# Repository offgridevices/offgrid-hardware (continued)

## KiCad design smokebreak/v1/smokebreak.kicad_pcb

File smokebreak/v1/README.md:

# SmokeBreak v1

**A smoke stopper you hold in one hand.** The battery plugs into one end and
the drone's lead into the other. Before the drone gets full battery power,
SmokeBreak checks it with a gentle 3 V probe. A short, a half-short or a
reversed lead is caught there, and nothing burns. The drone's capacitors are
then charged slowly through resistors. Only after that does the main switch
close, behind a guarded flip-up toggle.

Plug a pack's balance lead into its socket and SmokeBreak also reads every
cell (2S–6S), the pack's balance and its internal resistance. It remembers
each pack by number.

> **Status: design complete, not yet built.**
> - The board is fully routed: KiCad 10 DRC 0 errors, 0 warnings, 0 unconnected.
> - Its nets match the circuit pad for pad.
> - The power-path simulations pass (21 of 21), and so do the firmware model's 328 tests.
> - The printed case passes its fit check against the board.
>
> Nothing has been measured on hardware yet: build a few and go through
> *Bring-up* before a larger order.

## This revision

| | |
|---|---|
| Revision | **v1** (product: [`../README.md`](../README.md)) |
| Status | designed, not yet built |
| Tests and simulations | [`TESTS.md`](TESTS.md): every one with its v1 result |
| Trade-offs | [`docs/decisions.md`](docs/decisions.md) |
| Parts availability | [`docs/parts-check-2026-10-18.md`](docs/parts-check-2026-10-18.md) (check again before ordering) |
| How the circuit works | [`docs/architecture.md`](docs/architecture.md) |
| Spec, concepts, design studies | [`../design/`](../design/) (shared by every revision) |
| Toolchain | KiCad 10.0.7 (pinned image, `tools/Dockerfile`), Freerouting 2.5.0, ngspice 47, CadQuery 2.8 |
| Brand | OffGrid v3.2.2 ([`docs/brand.md`](../../docs/brand.md)); checked by `tools/verify_brand.py` |

| | |
|---|---|
| Case | 97 × 56 × 15 mm, G2 (curvature-continuous) corners, printed in three colours; the switch guard stands 17.9 mm above the face |
| Batteries | 2S–14S LiPo, LiHV, Li-ion (6–60.9 V); a 1S pack works when USB powers the box. XT60 and XT30 male |
| Drone | XT60 (12 AWG) and XT30 (16 AWG) female leads; 15 A continuous, 25 A for 60 s |
| Balance lead | five JST-XH sockets, 2S to 6S, in a well in the face |
| Screen | 2.25" 76 × 284 colour bar (EastRising ER-TFT2.25-1) |
| Controls | guarded flip-up toggle (up = on) inside a 12-LED status ring; one Limit rocker (− / +); beeper |
| Protection | 4 µs short-circuit cut-off, current limit, reversed-battery blocking on both sides, a 40 A fire fuse, refuses packs above 62.5 V |
| PCB | 91.6 × 50.6 mm, 6 layers, 1.6 mm, 1 oz copper on every layer, black mask, white silk, ENIG |

## Requirements

What the owner set, and where v1 stands.

| Requirement | v1 |
|---|---|
| Stops a short before it smokes | ✅ 3 V probe first; 4 µs cut-off when on (simulation case 3) |
| Survives wrong connections: reversed pack, pack on the drone side, both sides | ✅ simulations cases 2, 4, 5, 6 |
| Per-cell battery check, 2S–6S | ✅ divider network on 0.1 % resistors; firmware model tests |
| Fire safety if a part inside fails | ✅ soldered 40 A / 80 V fuse (`docs/decisions.md`) |
| Survives a pack bigger than 14S by mistake | ✅ 100 V supply chip; the screen says "too high" and it will not arm |
| Thin, small, one-hand use, does not rock when armed | ✅ 15 mm case, rubber feet, finger lip under the back edge |
| Perfectionist face: one 6 mm margin everywhere, G2 corners, screen corners matched in the UI | ✅ `src/geometry.py`, read by the board and the case |
| One rocker; text only "2S…6S" and "LIMIT" | ✅ multi-colour inlays, 2.5 mm caps, strokes ≥ 0.44 mm |
| Orderable from PCBWay, SMD parts assembled on one side | ✅ `production/` |
| Case printable on a multi-material printer | ✅ `enclosure/print/`: watertight STLs, fit check passes |
| Landed cost $20–22 (owner, 11 Oct 2026) | ❌ about **$55.60** at 100 units (`tools/cost.py`, display included): the two flat pre-charge resistors (≈ $14.70) and the toggle (≈ $10.20) are most of the gap. Accepted for v1 (owner, 1 Nov 2026); to bring down later (*Next steps*) |
| 15 A continuous in the closed case | ⏳ not yet checked for heat (*Limits*) |

## Next steps

1. **Bring the cost down (later).** v1 is accepted at about $55.60 (owner,
   1 Nov 2026). The places to look: same-footprint pre-charge resistors,
   and a short-lever toggle (which would also make the guard lower). Either
   part change re-runs the routing and every check, so it goes into `v2/`.
2. **Confirm the display's controller with EastRising.** The firmware
   model and the screens assume an ST7789P3. BuyDisplay's own page lists an
   **NV3023B** for the bare ER-TFT2.25-1, and the ST7789P3 for the
   ER-TFTM2.25-1 (the same panel on a breakout board). Ask which controller
   the bare module ships with. If it is the NV3023B, the firmware needs its
   driver (same pins, different init). Check the FPC's contact side against
   J7 too.
3. **Order 5 prototypes** (*Ordering*) and print one case (*Printing*).
4. **Bring them up** (*Bring-up*). Then measure what the simulations
   predict: pre-charge time and resistor heat, short cut-off time, and the
   temperature of the FETs at 15 A in the closed case. Record the results
   in `TESTS.md`.
5. **Write the real firmware** from the model in `firmware/` (every
   decision there is specified and tested).
6. Changes that need new copper go into `v2/`.

## Ordering the board (PCBWay)

1. **PCB:** upload `production/smokebreak-gerbers.zip`.
   - 6 layers, 91.6 × 50.6 mm, FR-4 TG150, 1.6 mm.
   - **1 oz copper on the outer and the inner layers** (the battery current runs on the inner planes).
   - Min track/space 4/4 mil, min hole 0.2 mm.
   - **Black** mask, **white** silkscreen, **ENIG**, vias tented.
2. **Assembly:** turnkey, top side only. Upload
   `production/smokebreak-bom-pcbway.csv` and `production/smokebreak-cpl.csv`.
   - LCSC has no stock of the fuse (**2822HC40-RTR**) or the pre-charge
     resistors (**D2TO020C3R900FRE3**), and only 3 of the TVS diode
     (**SMBJ64CA**) on 18 Oct 2026. Their BOM lines ask PCBWay to source the
     first two by part number from Digi-Key or Mouser. The TVS is a standard
     part that several makers produce. Details:
     [`docs/parts-check-2026-10-18.md`](docs/parts-check-2026-10-18.md).
   - The THT lines are not fitted; they ship loose: XT60PW-M, XT30PW-M,
     JST B3B/B4B/B5B/B6B/B7B-XH-A (one each), the C&K 7107 toggle, and the
     two drone leads (XT60H female on 12 AWG, XT30U female on 16 AWG, 50–75 mm).
3. **Display:** EastRising ER-TFT2.25-1 (76 × 284, 8-pin 0.5 mm FPC),
   bought separately. Ask for the IPS version.

## Printing the case

The files are in `enclosure/print/`. Use a 0.4 mm nozzle, 0.2 mm layers,
and PETG or ASA (PLA softens in a hot car).

| Part | Colour | Orientation | Notes |
|---|---|---|---|
| `top.stl` | main | face down | supports only inside the balance well (its floor plate is a bridge 2.7 mm up) |
| `text_inlay.stl` | white | with the top | same print job, second filament |
| `ring_inlay.stl` | translucent | with the top | same print job, third filament |
| `bottom.stl` | main | inside up | flat |
| `guard.stl` | accent | on its side | |
| `rocker.stl` | main | cap down | |

Hardware:
- 3 × M3 heat-set inserts (M3 × 5.7)
- 3 × M3 × 8 button-head screws
- 4 × Ø10 mm rubber feet (Bumpon)
- a Ø2 × 20 mm steel dowel (guard hinge)
- a Ø2 × 12 mm steel dowel (rocker pivot)
- a Ø6 × 3 mm N52 disc magnet (glued into the guard's tip)

The STEP models of every part, and the assembly, are in
`mechanical/smokebreak-enclosure-step.zip`. The fit check's full report is
`enclosure/print/fit_check.txt`.

## Assembly

1. **Balance sockets:** J12 (2S), J11 (3S), J10 (4S), J9 (5S) and J5 (6S),
   mouths up. Pin 1 (the square pad) goes at the front. The bottom silkscreen
   names each socket and points an arrow at pin 1 (the black wire).
2. **Battery plugs:** XT60 (J1) and XT30 (J2) male at the battery end. Seat
   them fully and use a big iron (the pads sit on power planes).
3. **Drone leads:** strip 5 mm and tin. The XT60 lead goes to J3 and the
   XT30 lead to J4, red to + (marked on both sides of the board).
4. **Toggle SW1 last,** lever upright.
5. **Trim every lead to 1.0 mm or less** under the board (the floor leaves 1.3 mm).
6. **Case:**
   1. Press the inserts into the top shell.
   2. Slide the guard's pin along its groove, then fit the guard.
   3. Fit the rocker and its pin.
   4. Tape the display into its pocket, with the FPC folded under to J7.
   5. Drop the board in.
   6. Hook the floor's tongue into the battery-end groove and close the
      floor. Its end tab clamps the drone leads.
   7. Fit the three screws.

## Bring-up

1. **Bare board:** check there are no shorts VIN–GND, VOUT–DRONE_NEG,
   +5V–GND or +3V3–GND.
2. **USB-C only:** +5V should read about 4.7 V and +3V3 should read 3.3 V.
   Flash over the SWD pads on the underside (J6) or USB DFU.
3. **Bench supply** at 12 V with a 100 mA limit, into the battery XT60,
   guard closed. The screen wakes, and nothing appears on the drone side.
4. **Reverse the bench supply:** nothing happens and nothing gets warm.
5. **Probe tests** with resistors on the drone side: open, 1 kΩ, 18 Ω,
   0.3 Ω. Then a 2200 µF capacitor bank for the pre-charge. Then a real drone.
6. **Measure and set in firmware:** the board's own capacitance on VOUT as
   the probe sees it, the current amplifier's offset, and the cell-divider gains.

## Limits

- **Heat at 15 A is not simulated.** The FETs (Q1, Q2 about 4 mΩ each, Q11
  about 8 mΩ) make about 4 W together at 15 A inside a closed printed case.
  Measure at bring-up before rating the box above short motor tests.
- **The pre-charge resistors' pulse rating** is read off the datasheet
  curve (about 10 J each at 100 ms). The firmware's 12 J abort puts 6 J on
  each. Bench-test repeated attempts and set the cool-down from the
  thermistor.
- **1S packs** need USB power: the 5 V supply starts at 6 V.
- **The guard sensor** reads "open" only once the guard is past about 40°.
  A guard that is only partly lifted counts as closed.
- **Simulation open risks** (models read off datasheet graphs, the short
  cut-off timing, capacitor DC bias) are listed in `sim/SIM.md`.

## Building it again

Everything here is generated by the scripts in `src/`, `enclosure/` and
`sim/`. Run them inside the pinned toolchain (`tools/Dockerfile`; `tools/kd`
runs a command in it).

| What | Command (from `smokebreak/v1`) | Notes |
|---|---|---|
| Silkscreen art on the routed board | `python3 src/artwork.py` | what CI runs |
| Production files, STEP, renders, DRC and net gates | `python3 src/fab.py` | `--no-3d` for the production files and gates only |
| Check the committed files | `python3 tools/check_outputs.py` | after the two above |
| Firmware model tests | `python3 -m pytest -q firmware/tests` | |
| Simulations | `cd sim && python3 run_all.py` | writes `sim/SIM.md` and `sim/plots/` |
| Brand check | `python3 tools/verify_brand.py` | needs Chromium |
| Case | `python3 enclosure/dump_board.py` (KiCad's Python), then `enclosure.py --no-dump` and `check.py` (a Python with CadQuery 2.8 and trimesh), `render.py` (Blender's Python, previews), `package.py` | see `enclosure/README.md` |
| The whole board from the circuit | `bash src/pipeline.sh` | about 3 hours; routing differs run to run, so the committed board stays the design of record |

The routed board (`smokebreak.kicad_pcb`) is the design of record. CI does
not route the board again; it rebuilds the art and every production file from
the routed board, and fails if they differ from what is committed.

## What is where

| Path | What |
|---|---|
| `smokebreak.kicad_pcb` / `.kicad_pro` / `.kicad_dru` | the routed board (KiCad 10) |
| `production/` | Gerber zip, PCBWay BOM, pick-and-place, netlist |
| `mechanical/` | the board in 3D (`smokebreak-step.zip`), the case parts in 3D (`smokebreak-enclosure-step.zip`) |
| `enclosure/` | the case as code (CadQuery), its fit check, and `print/` (the STLs) |
| `images/` | renders of the board and the case |
| `src/` | the board as code: `geometry.py` (every mechanical number), `circuit.py`, `parts.py`, `place.py`, the router steps, `artwork.py`, `fab.py` |
| `lib/` | footprints and 3D models |
| `fonts/` | the brand fonts the silkscreen and case text are drawn in (OFL) |
| `sim/` | power-path simulations and their report |
| `firmware/` | reference model of every firmware decision, with tests |
| `ui/` | the screens, drawn at the panel's real resolution |
| `tools/` | toolchain (Dockerfile), output check, brand check, cost tally, debug plots |
| `docs/` | decisions, architecture, the dated parts check |
| [`../design/`](../design/) | before any revision: the original spec, market research, the 20 concepts and the design studies |

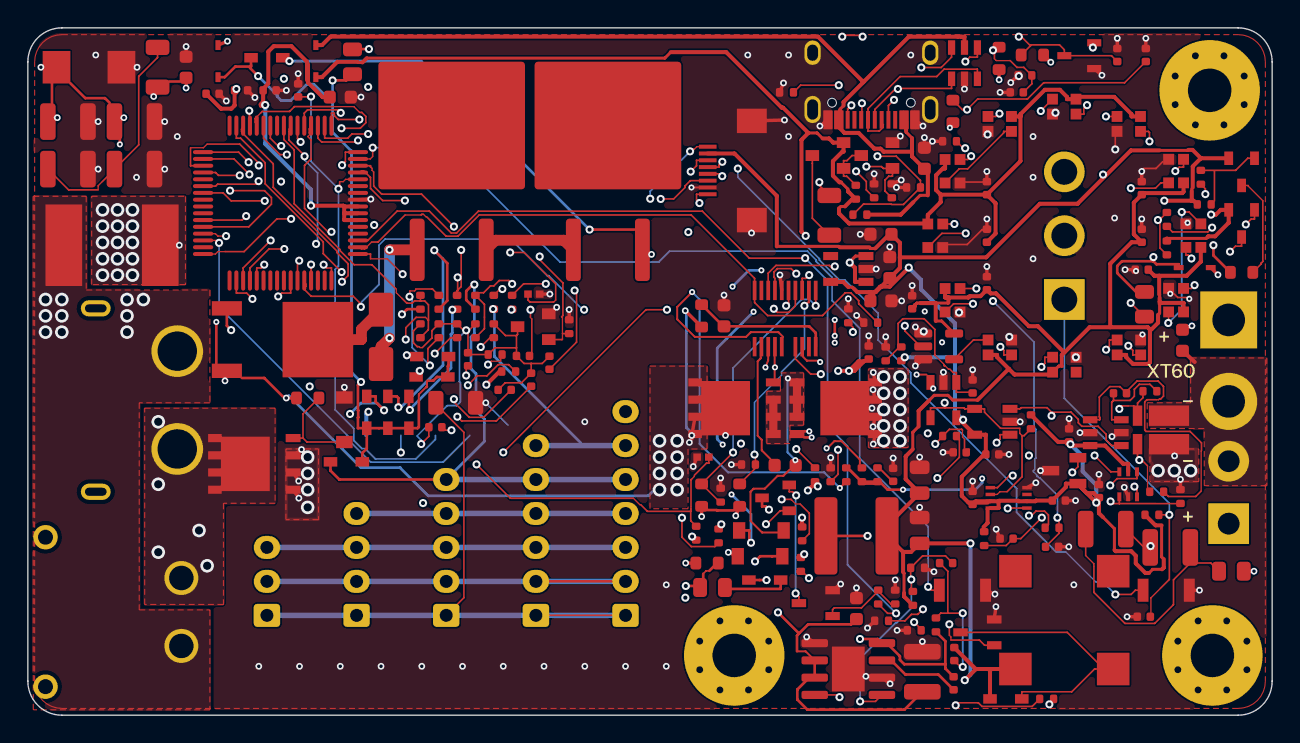
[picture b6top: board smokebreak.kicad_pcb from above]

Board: 6 copper layers, 91.6 x 50.6 mm, 208 parts (1 on the bottom side), 123 nets.

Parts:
BZ1: MLT-8530; BUZ-SMD_4P-L8.5-W8.5-P8.50-BR
C1, C2, C26: 2u2F 100V; C_1210_3225Metric
C3, C4, C14, C27: 100nF 100V; C_0603_1608Metric
C5, C32, C41, C49: 1uF 25V; C_0603_1608Metric
C6, C8, C16: 1nF 50V; C_0402_1005Metric
C7, C10, C11, C12, C13, C15, C17, C18, C19, C20, C21, C22, C23, C34, C35, C36, C38, C42, C43, C44, C45, C46, C47, C48, C55, C56: 100nF 16V; C_0402_1005Metric
C9, C39, C40: 10nF 50V; C_0402_1005Metric
C28: 3n3F 50V; C_0402_1005Metric
C29: 2n2F 50V; C_0402_1005Metric
C30, C31: 10uF 10V; C_0805_2012Metric
C33, C37: 4u7F 10V; C_0603_1608Metric
C50, C51, C52, C53: 4u7F 100V; C_1210_3225Metric
C54: 22nF 50V; C_0402_1005Metric
C57: 56pF 50V; C_0402_1005Metric
D1: SMBJ64CA; SMB_L4.6-W3.6-LS5.3-BI
D2: 10 V; SOD-123_L2.7-W1.6-LS3.7-RD
D3: SS2H10; D_SMA
D4, D14, D16: BAT46WJ; SOD-323F_L2.0-W1.6-LS2.5-RD
D5: BAT54S; SOT-23-3_L3.0-W1.7-P0.95-LS2.9-BR
D6, D7, D8, D9, D10, D11, D15, D17, D19: 1N4148WS; SOD-323_L1.8-W1.3-LS2.5-RD
D18: 15 V; SOD-123_L2.7-W1.6-LS3.7-RD
D20: 12 V; SOD-123_L2.7-W1.6-LS3.7-RD
F1: 40 A 80 V; Fuse_Eaton_2822HC
H1, H2, H3: M3; MountingHole_M3_Washer
J1: XT60 male; CONN-TH_XT60PW-M
J2: XT30 male; CONN-TH_XT30PW-M
J3: XT60 female lead; WirePads_12AWG_NS
J4: XT30 female lead; WirePads_16AWG_NS
J5: JST-XH 6S; JST_XH_B7B-XH-A_1x07_P2.50mm_Vertical_Tight
J6: SWD; SWD_Pads_1x5_P2.54
J7: ER-TFT2.25-1 FPC; Hirose_FH12-8S-0.5SH_1x08-1MP_P0.50mm_Horizontal
J8: USB-C; USB-C_SMD-TYPE-C-31-M-12_1
J9: JST-XH 5S; JST_XH_B6B-XH-A_1x06_P2.50mm_Vertical_Tight
J10: JST-XH 4S; JST_XH_B5B-XH-A_1x05_P2.50mm_Vertical_Tight
J11: JST-XH 3S; JST_XH_B4B-XH-A_1x04_P2.50mm_Vertical_Tight
J12: JST-XH 2S; JST_XH_B3B-XH-A_1x03_P2.50mm_Vertical_Tight
L1: 47 uH; L_Changjiang_FNR6045S
LED1, LED2, LED3, LED4, LED5, LED6, LED7, LED8, LED9, LED10, LED11, LED12: WS2812B-2020; LED-SMD_4P-L2.2-W2.0-P1.00_WS2815C-2020-4P
Q1: input FET; PG-TDSON-8_L5.9-W5.1-P1.27-LS6.1-BL
Q2: output FET; PG-TDSON-8_L5.9-W5.1-P1.27-LS6.1-BL
Q3: SUD50P10-43L; TO-252-3_L6.5-W5.8-P4.58-BR
Q4: MMBTA42; SOT-23-3_L2.9-W1.3-P1.90-LS2.4-BR
Q5, Q10: BC817; SOT-23-3_L2.9-W1.6-P1.90-LS2.8-BR
Q6, Q7: MMBT5401; SOT-23-3_L2.9-W1.3-P1.90-LS2.4-BR
Q8, Q12: 2N7002; SOT-23_L2.9-W1.3-P1.90-LS2.4-BR
Q9: AO3401A; SOT-23_L2.9-W1.3-P1.90-LS2.4-BR
Q11: BSC070N10LS5; PG-TDSON-8_L5.9-W5.1-P1.27-LS6.1-BL
R1: 10 Ohm; R_0603_1608Metric
R2, R4, R30, R33: 1 M; R_0603_1608Metric
R3: 470 k; R_0402_1005Metric
R5: 19.6 k; R_0402_1005Metric
R6, R10, R13, R18, R23, R24, R26, R27, R37, R39, R41, R43, R45, R47, R52, R60, R64, R65, R79, R80: 100 k; R_0402_1005Metric
R7: 1 M; R_0402_1005Metric
R8, R11, R12, R21, R22, R25, R35, R66: 10 k; R_0402_1005Metric
R9: 40.2 k; R_0402_1005Metric
R14, R15: 10 Ohm; R_0402_1005Metric
R16: 100 Ohm; R_0402_1005Metric
R17, R54, R55, R61, R69, R71: 1 k; R_0402_1005Metric
R19, R32: 100 k; R_0603_1608Metric
R20: 47 k; R_0805_2012Metric
R28: 1 k; R_0603_1608Metric
R29: 100 Ohm; R_0805_2012Metric
R31, R34: 52.3 k; R_0402_1005Metric
R36: 47 k; R_0402_1005Metric
R38: 200 k; R_0402_1005Metric
R40: 357 k; R_0402_1005Metric
R42: 499 k; R_0402_1005Metric
R44: 649 k; R_0402_1005Metric
R46: 787 k; R_0402_1005Metric
R53: 10 Ohm; R_0805_2012Metric
R56: 33 Ohm; R_1206_3216Metric
R62, R63: 5.1 k; R_0402_1005Metric
R67: 0.33 Ohm; R_1206_3216Metric
R68: 0.47 Ohm; R_0805_2012Metric
R70: 49.9 k; R_0402_1005Metric
R72: 4.7 k; R_0402_1005Metric
R73: 820 Ohm; R_0402_1005Metric
R74: 4.7 M; R_0603_1608Metric
R75: 10 Ohm; R_1206_3216Metric
R76: 30.9 k; R_0402_1005Metric
R77: 453 k; R_0402_1005Metric
R78: 143 k; R_0402_1005Metric
RS1: 1 mOhm; RES-SMD_4P-L3.8-W3.1
RT1, RT2: 10 k NTC; R0402
R_PRE, R_PRE2: 3.9 Ohm 20 W; TO-263-2
SW1: ON-OFF-(ON); SW_Toggle_SPDT_P4.70mm_THT
SW2: Limit -; KEY-SMD_B3U-1000PM
SW3: Limit +; KEY-SMD_B3U-1000PM
U1: TPS48000; VSSOP-19_L5.1-W3.0-P0.50-LS4.9
U2: INA181A2; SOT-23-6_L2.9-W1.6-P0.95-LS2.8-BL
U3: LM5164DDAR; SOIC-8-1EP_3.9x4.9mm_P1.27mm_EP2.41x3.3mm
U4: TLV75533; SOT-23-5_L3.0-W1.7-P0.95-LS2.8-BR
U5: STM32G0B1RBT6; LQFP-64_L10.0-W10.0-P0.50-LS12.0-BL
U6: DRV5032FA; SOT-23-3_L2.9-W1.3-P0.95-LS2.4-BR
U7: 74LVC1G11; SC-88-6_L2.0-W1.3-P0.65-LS2.1-BL
U8, U12: LMV331; SOT-23-5_L3.0-W1.7-P0.95-LS2.8-BR
U9: SN74LVC1G74; SSOP-8_L2.0-W2.3-P0.50-LS3.1-BR
U10: SN74AHCT1G125; SOT-23-5
U11: USBLC6-2SC6; SOT-23-6_L2.9-W1.6-P0.95-LS2.8-BL

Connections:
+3V3: C7.1, C10.1, C11.1, C12.1, C13.1, C32.1, C33.1, C34.1, C35.1, C36.1, C37.1, C41.1, C56.1, D5.2, J6.1, J7.7, Q6.2, Q7.2, R8.1, R11.2, R12.2, R25.1, R26.2, R27.2, R35.1, R54.2, R55.2, R66.2, R70.1, U2.6, U4.5, U5.6, U5.7, U5.8, U6.1, U7.5, U8.5, U9.2, U9.7, U9.8, U12.5
+5V: BZ1.1, C28.2, C30.1, C31.1, C42.1, C43.1, C44.1, C45.1, C46.1, C47.1, C48.1, D16.1, D17.1, L1.2, LED1.4, LED2.4, LED3.4, LED4.4, LED5.4, LED6.4, LED7.4, LED8.4, LED9.4, LED10.4, LED11.4, LED12.4, Q9.2, R77.1, R80.1, U4.1, U4.3, U10.5
ARM_CLK: U5.60, U9.1
AUX: D6.1, D7.1, D8.1, D9.1, D10.1, D11.1, D14.1, D15.1, R53.1
AUX_F: C26.1, C27.1, R53.2, U3.2, U3.3
BAL1: J5.1, J9.1, J10.1, J11.1, J12.1, R75.1
BAL2: D6.2, J5.2, J9.2, J10.2, J11.2, J12.2, R36.1
BAL2_ADC: C18.1, R36.2, R37.1, U5.24
BAL3: D7.2, J5.3, J9.3, J10.3, J11.3, J12.3, R38.1
BAL3_ADC: C19.1, R38.2, R39.1, U5.27
BAL4: D8.2, J5.4, J9.4, J10.4, J11.4, R40.1
BAL4_ADC: C20.1, R40.2, R41.1, U5.28
BAL5: D9.2, J5.5, J9.5, J10.5, R42.1
BAL5_ADC: C21.1, R42.2, R43.1, U5.29
BAL6: D10.2, J5.6, J9.6, R44.1
BAL6_ADC: C22.1, R44.2, R45.1, U5.30
BAL7: D11.2, J5.7, R46.1
BAL7_ADC: C23.1, R46.2, R47.1, U5.31
BATT_NEG: J1.1, J2.1, Q11.5, Q11.6, Q11.7, Q11.8
BL_G: Q9.1, Q12.3, R80.2
BL_SW: Q9.3, R56.1
BTN_MINUS: SW2.1, U5.15
BTN_PLUS: SW3.1, U5.16
BUCK_BOOT: C29.1, U3.7
BUCK_FB: C57.2, R77.2, R78.1, U3.5
BUCK_RA: C28.1, C57.1, R79.2
BUCK_RON: R76.1, U3.4
BUCK_SW: C29.2, L1.1, R79.1, U3.8
BUZZER: R61.1, U5.36
BZ_B: Q10.1, R61.2
BZ_N: BZ1.2, D17.2, Q10.3
CDVDT: C54.1, R69.2
DIV_EN: Q8.1, R52.1, U5.53
DIV_GND: C18.2, C19.2, C20.2, C21.2, C22.2, C23.2, Q8.3, R37.2, R39.2, R41.2, R43.2, R45.2, R47.2
DRONE_NEG: C14.2, C52.2, C53.2, J3.2, J4.2, RS1.1
GATE: D18.1, Q1.4, Q2.4, R6.2, R7.1, R69.1, U1.14
GND: C1.2, C2.2, C3.2, C4.2, C7.2, C8.2, C9.2, C10.2, C11.2, C12.2, C13.2, C15.2, C16.2, C17.2, C26.2, C27.2, C30.2, C31.2, C32.2, C33.2, C34.2, C35.2, C36.2, C37.2, C38.2, C39.2, C40.2, C41.2, C42.2, C43.2, C44.2, C45.2, C46.2, C47.2, C48.2, C49.2, C50.2, C51.2, C54.2, C55.2, C56.2, D1.2, D5.1, D20.2, J6.5, J7.2, J7.MP, J8.1, J8.2, J8.3, J8.4, J8.A1B12, J8.B1A12, LED1.2, LED2.2, LED3.2, LED4.2, LED5.2, LED6.2, LED7.2, LED8.2, LED9.2, LED10.2, LED11.2, LED12.2, Q5.2, Q8.2, Q10.2, Q11.1, Q11.2, Q11.3, Q12.2, R3.2, R5.2, R9.2, R10.2, R13.2, R18.2, R23.2, R24.2, R31.2, R34.2, R52.2, R60.2, R62.2, R63.2, R65.2, R71.2, R75.2, R76.2, R78.2, RS1.4, RT1.2, RT2.2, SW1.2, SW2.2, SW3.2, U1.6, U2.2, U2.5, U3.1, U3.6, U3.9, U4.2, U5.9, U6.3, U7.2, U8.2, U9.4, U10.1, U10.3, U11.2, U12.2
GUARD_OPEN: R22.1, U5.3, U6.2, U7.3
HS_REF: C55.1, R70.2, R71.1, U12.1
INA_N: C6.2, R15.2, U2.4
INA_P: C6.1, R14.2, U2.3
I_ADC: C8.1, R16.2, U5.20
I_SENSE: R16.1, U2.1, U8.3
LATCH_OK: U7.6, U9.5
LCD_BL: Q12.1, R60.1, U5.48
LCD_CS: J7.8, U5.34
LCD_DC: J7.4, U5.38
LCD_LEDA: J7.1, R56.2
LCD_RST: J7.3, U5.39
LCD_SCK: J7.6, U5.33
LCD_SDA: J7.5, U5.35
LED_D1: LED1.1, LED2.3
LED_D2: LED2.1, LED3.3
LED_D3: LED3.1, LED4.3
LED_D4: LED4.1, LED5.3
LED_D5: LED5.1, LED6.3
LED_D6: LED6.1, LED7.3
LED_D7: LED7.1, LED8.3
LED_D8: LED8.1, LED9.3
LED_D9: LED9.1, LED10.3
LED_D10: LED10.1, LED11.3
LED_D11: LED11.1, LED12.3
LED_DATA: U5.59, U10.2
LED_DIN0: LED1.3, U10.4
MCU_EN: R18.1, U5.58, U7.1
NRST: C38.1, J6.3, U5.12
NTC_FET: R35.2, RT1.1, U5.22
NTC_PRE: R25.2, RT2.1, U5.23
PEAK_DAC: R17.1, U5.21
PEAK_OK: R66.1, U5.61, U8.4, U9.6, U12.4
PEAK_REF: C9.1, R17.2, U8.1
PRE_B1: Q4.1, R21.2, R23.1
PRE_B2: Q5.1, R22.2, R24.1
PRE_D: D3.2, Q3.2
PRE_G: D2.2, Q3.1, R19.2, R20.1
PRE_K: D3.1, R_PRE.1
PRE_M: R_PRE.3, R_PRE2.1
PRE_MID: Q4.2, Q5.3
PRE_ON: R21.1, U5.50
PRE_PULL: D19.1, Q4.3
PRE_R: D19.2, R20.2
PROBE: D4.2, R28.2, R29.2
PROBE_1K_N: R72.1, U5.51
PROBE_100_N: R73.1, U5.52
PROBE_A: Q6.3, R28.1
PROBE_B: Q7.3, R29.1
PROBE_BB1: Q6.1, R26.1, R72.2
PROBE_BB2: Q7.1, R27.1, R73.2
Q11_G: D20.1, Q11.4, R74.2
SNS_DRN: R14.1, RS1.2, U1.18, U12.3
SNS_GND: R15.1, RS1.3, U1.17
SRC: C5.2, D18.2, Q1.1, Q1.2, Q1.3, Q2.1, Q2.2, Q2.3, R7.2, U1.13
SWCLK: J6.4, U5.46
SWDIO: J6.2, U5.45
TOG_BIND: C40.1, R55.1, SW1.1, U5.14
TOG_ON: C39.1, R54.1, SW1.3, U5.13
TPS_BST: C5.1, U1.12
TPS_CSSEL: R8.2, U1.7
TPS_EN: R2.2, R3.1, U1.1
TPS_FLT: R11.1, U1.5, U5.64
TPS_FLTGD: R12.1, U1.4, U5.1
TPS_INP: R13.1, U1.3, U7.4
TPS_ISCP: R9.1, U1.8
TPS_OV: R4.2, R5.1, U1.2
TPS_PU: R6.1, U1.15
TPS_SCPTEST: R10.1, U1.10, U5.2
TPS_VS: C4.1, R1.2, U1.20
USB_CC1: J8.A5, R62.1
USB_CC2: J8.B5, R63.1
USB_DM: U5.43, U11.4
USB_DM_C: J8.A7, J8.B7, U11.3
USB_DP: U5.44, U11.6
USB_DP_C: J8.A6, J8.B6, U11.1
VBAT: F1.1, J1.2, J2.2
VBUS: C49.1, D16.2, J8.A4B9, J8.B4A9, R64.1, U11.5
VBUS_SENSE: R64.2, R65.1, U5.26
VIN: C1.1, C2.1, C3.1, D1.1, D2.1, D14.2, F1.2, Q1.5, Q1.6, Q1.7, Q1.8, Q3.3, R1.1, R2.1, R4.1, R19.1, R33.1, R67.1, R74.1
VIN_DAMP: C50.1, C51.1, R67.2
VIN_SENSE: C17.1, R33.2, R34.1, U5.17
VOUT: C14.1, D4.1, D15.2, J3.1, J4.1, Q2.5, Q2.6, Q2.7, Q2.8, R30.1, R32.1, R68.1, R_PRE2.3
VOUT_LO: C16.1, D5.3, R32.2, U5.19
VOUT_SENSE: C15.1, R30.2, R31.1, U5.18
VOUT_SNUB: C52.1, C53.1, R68.2

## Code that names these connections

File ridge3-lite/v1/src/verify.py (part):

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
# ------------------------------------------------------------------ FC
FC_MAP = {   # TAKERG4AIO define -> net on this board (None: pin left open)
    'MOTOR1_PIN': 'M1_SIG', 'MOTOR2_PIN': 'M2_SIG', 'MOTOR3_PIN': 'M3_SIG', 'MOTOR4_PIN': 'M4_SIG',
    'GYRO_1_EXTI_PIN': 'GYRO_INT', 'GYRO_1_CS_PIN': 'GYRO_CS', 'SPI1_SCK_PIN': 'SPI1_SCK',
    'SPI1_SDI_PIN': 'SPI1_MISO', 'SPI1_SDO_PIN': 'SPI1_MOSI', 'UART1_TX_PIN': 'UART1_TX',
    'UART1_RX_PIN': 'UART1_RX', 'UART2_TX_PIN': 'UART2_TX', 'UART2_RX_PIN': 'UART2_RX',
    'LED0_PIN': 'LED0', 'LED_STRIP_PIN': 'LED_STRIP', 'BEEPER_PIN': 'BEEPER', 'ADC_VBAT_PIN': 'ADC_VBAT',
    'ADC_CURR_PIN': 'CUR', 'FLASH_CS_PIN': None, 'MAX7456_SPI_CS_PIN': None, 'SPI2_SCK_PIN': None,
    'SPI2_SDI_PIN': None, 'SPI2_SDO_PIN': None, 'UART4_TX_PIN': None, 'UART4_RX_PIN': None,
    'LPUART1_TX_PIN': None, 'LPUART1_RX_PIN': None,
}

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        got = u.pins.get(pin)
        check(S, '%s %s (pin %s) carries %s' % (d, p, pin, net or 'nothing'), got == net,
              'circuit.py: %s' % got)
    for p, net in (('PA11', 'USB_DM'), ('PA12', 'USB_DP'), ('PF0', 'HSE_IN'), ('PF1', 'HSE_OUT'), ('PB8', 'BOOT0')):
        check(S, '%s (pin %s) carries %s' % (p, port[p], net), u.pins.get(port[p]) == net)
    pw = [n for n, nm in sym.items() if re.match(r'(VDD|VDDA|VREF\+|VBAT)$', nm)]
    check(S, 'every VDD / VDDA / VREF+ / VBAT pin on +3V3 (%s)' % ','.join(sorted(pw, key=int)),
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        want[pinof(gd['PHASE_%s_GPIO_PORT_HIGH' % ph][-1], gd['PHASE_%s_GPIO_HIGH' % ph])] = 'H' + ph
        cm = re.search(r'#define PHASE_%s_COMP\s+\S+\s*//\s*(p[a-z]\d+)' % ph, g)
        want[cm.group(1).upper()] = 'CMP_' + ph
    cur = re.search(r'#define CURRENT_ADC_PIN LL_GPIO_PIN_(\d+)', mcu.split('#ifdef MCU_G031')[0])
    vol = re.search(r'#define VOLTAGE_ADC_PIN LL_GPIO_PIN_(\d+)', mcu.split('#ifdef MCU_G031')[0])
    want['PA%s' % cur.group(1)] = 'ISENSE'
    want['PA%s' % vol.group(1)] = 'VSENSE'
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        u = comp('U_E%d' % n)
        bad = [(p, port.get(p), u.pins.get(port.get(p)), 'M%d_%s' % (n, f)) for p, f in sorted(want.items())
               if u.pins.get(port.get(p)) != 'M%d_%s' % (n, f)]
        check(S, 'ESC %d: input, 6 gate outputs, 3 comparators, neutral, current, voltage on AM32\'s pins' % n,
              not bad, ', '.join('%s %s' % (p, f) for p, f in sorted(want.items())) if not bad else str(bad))
        check(S, 'ESC %d: VDD/VDDA on +3V3E, VSS on GND' % n, u.pins.get('3') == '+3V3E' and u.pins.get('4') == 'GND')
    check(S, 'remap: PA11/PA12 pads carry PA9/PA10 (AM32 enables the remap: NO_PA11_PA12_REMAP unset)',
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
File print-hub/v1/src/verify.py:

# -*- coding: utf-8 -*-
"""Design checks that tie the firmware, the circuit and the parts together.
Writes ../VERIFICATION.md; exits 1 if any check fails.

    python3 src/verify.py

  * firmware pin map (firmware/src/board.h) against circuit.py: every pin
    the firmware drives or reads is wired to the net it means
  * the firmware's scaling (shunt, gain, dividers) against the parts
  * the LED chain order against the firmware's LED index
  * ESP32-S3 rules: analogue inputs on ADC1 only (ADC2 stops while Wi-Fi
    is on), strapping pins left alone, native USB on GPIO19/20
  * every port: switch, enable pull-down, fault pull-up, shunt, amplifier,
    DCP short on the USB-A
  * the simulations' own verdicts (sim/*.md)
"""
import os, re, sys
HERE = os.path.dirname(os.path.abspath(__file__))
V1 = os.path.dirname(HERE)
sys.path.insert(0, HERE)
import circuit, parts

# ESP32-S3-WROOM-1 module pin -> GPIO (Espressif datasheet, pin layout)
MODULE_GPIO = {4: 4, 5: 5, 6: 6, 7: 7, 8: 15, 9: 16, 10: 17, 11: 18, 12: 8, 13: 19, 14: 20, 15: 3, 16: 46,
               17: 9, 18: 10, 19: 11, 20: 12, 21: 13, 22: 14, 23: 21, 24: 47, 25: 48, 26: 45, 27: 0,
               28: 35, 29: 36, 30: 37, 31: 38, 32: 39, 33: 40, 34: 41, 35: 42, 36: 44, 37: 43, 38: 2, 39: 1}
ADC1 = set(range(1, 11))
STRAPPING = {3, 45, 46}

results = []


def check(ok, what):
    results.append((bool(ok), what))
    return ok


def firmware_pins():
    src = open(os.path.join(V1, 'firmware', 'src', 'board.h')).read()
    pins = {}
    for m in re.finditer(r'constexpr uint8_t (\w+)(\[[^\]]*\])? = (\{[^}]*\}|\d+);', src):
        name, val = m.group(1), m.group(3)
        pins[name] = [int(v) for v in re.findall(r'\d+', val)] if val.startswith('{') else int(val)
    scale = {}
    for m in re.finditer(r'constexpr float (\w+) = ([^;]+);', src):
        scale[m.group(1)] = m.group(2)
    return pins, scale


def value_ohms(v):
    m = re.match(r'([\d.]+)\s*(m|k|R)?', v.replace('mR', 'm').replace('Ohm', ''))
    x = float(m.group(1))
    return x * {'m': 1e-3, 'k': 1e3, 'R': 1, None: 1}[m.group(2)]


def main():
    comps = circuit.build()
    by_ref = {c.ref: c for c in comps}
    esp = next(c for c in comps if c.part == 'ESP32S3')
    gpio_net = {MODULE_GPIO[int(p)]: n for p, n in esp.pins.items() if int(p) in MODULE_GPIO}
    pins, scale = firmware_pins()
    n = circuit.NPORTS

    # ---- pin map
    for i in range(n):
        check(gpio_net.get(pins['EN'][i]) == 'EN%d' % (i + 1), 'USB%d enable: firmware GPIO%d is %s' % (i + 1, pins['EN'][i], gpio_net.get(pins['EN'][i])))
        check(gpio_net.get(pins['FLT'][i]) == 'FLT%d' % (i + 1), 'USB%d fault: firmware GPIO%d is %s' % (i + 1, pins['FLT'][i], gpio_net.get(pins['FLT'][i])))
        check(gpio_net.get(pins['ISENSE'][i]) == 'IS%d' % (i + 1), 'USB%d current: firmware GPIO%d is %s' % (i + 1, pins['ISENSE'][i], gpio_net.get(pins['ISENSE'][i])))
    for name, net in (('VIN_SENSE', 'VIN_SENSE'), ('RAIL_SENSE', 'RAIL_SENSE'), ('LED_DATA', 'LED_DIN0'),
                      ('I2C_SDA', 'SDA'), ('I2C_SCL', 'SCL'), ('BUTTON', 'BOOT')):
        check(gpio_net.get(pins[name]) == net, '%s: firmware GPIO%d is %s' % (name, pins[name], gpio_net.get(pins[name])))
    check(gpio_net.get(19) == 'USB_DN' and gpio_net.get(20) == 'USB_DP', 'native USB: GPIO19 = D-, GPIO20 = D+')
    adc = list(pins['ISENSE']) + [pins['VIN_SENSE'], pins['RAIL_SENSE']]
    check(all(g in ADC1 for g in adc), 'every analogue input on ADC1 (GPIO1-10): %s' % adc)
    check(all(gpio_net.get(g) is None for g in STRAPPING), 'strapping pins GPIO3, 45, 46 left open')
    check(len(set(gpio_net[g] for g in gpio_net if gpio_net[g])) == len([g for g in gpio_net if gpio_net[g]]),
          'no two GPIOs on one net')

    # ---- scaling
    shunt = next(c for c in comps if c.part == 'SHUNT20M')
    rs = value_ohms(parts.PARTS[shunt.part]['value'])
    check(abs(eval(scale['SHUNT_OHM'].rstrip('f')) - rs) < 1e-9, 'shunt: firmware %s, part %g ohm' % (scale['SHUNT_OHM'], rs))
    check(parts.PARTS['INA180A2']['mpn'].startswith('INA180A2') and scale['AMP_GAIN'].startswith('50'),
          'amplifier gain: INA180A2 is 50 V/V, firmware %s' % scale['AMP_GAIN'])

    def divider(net):
        top = [c for c in comps if c.part.startswith('R') and net in c.pins.values() and
               any(v in ('VBUS_IN', 'VRAIL') for v in c.pins.values())]
        bot = [c for c in comps if c.part.startswith('R') and net in c.pins.values() and 'GND' in c.pins.values()]
        t, b_ = value_ohms(parts.PARTS[top[0].part]['value']), value_ohms(parts.PARTS[bot[0].part]['value'])
        return (t + b_) / b_
    for name, net in (('VIN_DIV', 'VIN_SENSE'), ('RAIL_DIV', 'RAIL_SENSE')):
        fw = eval(scale[name].replace('f', ''))
        check(abs(fw - divider(net)) < 1e-6, '%s: firmware %.4f, circuit %.4f' % (name, fw, divider(net)))

    # ---- LED chain: index k in the firmware is the k-th LED from the ESP32
    chain, net = [], 'LED_D0'
    while True:
        nxt = [c for c in comps if c.part == 'WS2812B' and c.pins.get('3') == net]
        if not nxt:
            break
        c = nxt[0]
        chain.append(c.block)
        net = c.pins.get('1')
        if not net:
            break
    want = ['logic'] + ['USB%d' % (n - k) for k in range(n)]
    check(chain == want, 'LED chain from the ESP32: %s (firmware: status, then USB%d .. USB1)' % (' > '.join(chain), n))
    mainsrc = open(os.path.join(V1, 'firmware', 'src', 'main.cpp')).read()
    check('board.set_led(hub::NPORTS - p' in mainsrc and 'board.set_led(0, st)' in mainsrc,
          'firmware LED index: status 0, port p at NPORTS - p')

    # ---- each port has its parts
    for i in range(1, n + 1):
        blk = [c for c in comps if c.block == 'USB%d' % i]
        has = lambda pred: any(pred(c) for c in blk)
        check(has(lambda c: c.part == 'TPS25200' and c.pins['6'] == 'VRAIL' and c.pins['4'] == 'EN%d' % i), 'USB%d: switch from the 5 V rail, enabled by EN%d' % (i, i))
        check(has(lambda c: c.part == 'R100K' and set(c.pins.values()) == {'EN%d' % i, 'GND'}), 'USB%d: enable pulled down (off during reset and flashing)' % i)
        check(has(lambda c: c.part == 'R10K' and set(c.pins.values()) == {'FLT%d' % i, '+3V3'}), 'USB%d: fault line pulled up to 3.3 V' % i)
        check(has(lambda c: c.part == 'R47K' and set(c.pins.values()) == {'ILIM%d' % i, 'GND'}), 'USB%d: 47k on ILIM (2.07 A)' % i)
        check(has(lambda c: c.part == 'USBA' and c.pins['2'] == c.pins['3'] and c.pins['1'] == 'VBUS%d' % i), 'USB%d: D+ joined to D- (BC1.2 charging port), VBUS from the shunt' % i)
        check(has(lambda c: c.part == 'INA180A2' and c.pins['3'] == 'PORT%d_SW' % i and c.pins['4'] == 'VBUS%d' % i and c.pins['5'] == '+3V3'),
              'USB%d: amplifier across the shunt, IN+ on the switch side, supplied from 3.3 V' % i)
    # the logic never feeds a port: VBUS_DATA reaches VLOGIC only through a diode
    d = [c for c in comps if c.part == 'B5819W']
    check(sorted((c.pins['2'], c.pins['1']) for c in d) == [('VBUS_DATA', 'VLOGIC'), ('VRAIL', 'VLOGIC')],
          'logic supply: VRAIL and VBUS_DATA each through a Schottky (anode) into VLOGIC (cathode)')
    check(not any('VBUS_DATA' in c.pins.values() and 'VRAIL' in c.pins.values() for c in comps),
          'nothing joins the print server\'s VBUS to the port rail')

    # ---- simulation verdicts
    for md in ('power_budget.md', 'port_events.md'):
        p = os.path.join(V1, 'sim', md)
        txt = open(p).read() if os.path.exists(p) else ''
        check(txt and 'FAIL' not in txt and 'PASS' in txt, 'simulation %s: all its checks pass' % md)

    out = ['# Print Hub v1: design checks', '', 'Written by `src/verify.py`. %d passed, %d failed.' %
           (sum(r[0] for r in results), sum(not r[0] for r in results)), '']
    out += ['- %s %s' % ('PASS' if ok else 'FAIL', w) for ok, w in results]
    open(os.path.join(V1, 'VERIFICATION.md'), 'w').write('\n'.join(out) + '\n')
    bad = [w for ok, w in results if not ok]
    print('%d checks, %d failed' % (len(results), len(bad)))
    for w in bad:
        print('  FAIL', w)
    return not bad


if __name__ == '__main__':
    sys.exit(0 if main() else 1)

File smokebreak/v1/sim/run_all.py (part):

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        ax[0, 0].plot(d["time"] * 1e3, d["vvout"], color=C[j], label=f"RPRE {r_:g} Ω")
    ax[0, 0].axhline(0.75 * 8 * 3.7, color=S.INK2, ls="--", lw=1)
    ax[0, 0].text(600, 0.75 * 8 * 3.7 - 1.6, "75 % of VIN", color=S.INK2)
    ax[0, 0].set(title="(a) 8S 3.7 V/cell, 2200 µF + 15 W VTX: VOUT vs RPRE", xlabel="ms", ylabel="V")
    ax[0, 0].legend(loc="lower right", fontsize=7)
    r = sw[(gsel, "14S LiHV, 5000 µF, 15 W")]
    d = r["d"]
    tt = (d["time"] - r["tmain"]) * 1e3
    ax[0, 1].plot(tt, d["vvin"], color=C[0], label="VIN")
    ax[0, 1].plot(tt, d["vvout"], color=C[1], label="VOUT")
    ax[0, 1].set(title=f"(b) 14S LiHV 5000 µF: settle, then close ({gsel})", xlabel="ms from INP high",
                 ylabel="V", xlim=(-100, 100), ylim=(50, 63))
    ax[0, 1].legend()
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    ax[0].axhline(90, color=C[7], ls="--", lw=1)
    ax[1].axhline(-65, color=C[7], ls="--", lw=1)
    ax[0].set(title="Forward 14S LiHV plug-in: VIN (Q1 drain)", xlabel="µs", ylabel="V", xlim=(-0.5, 20))
    ax[1].set(title="Reversed 14S LiHV plug-in: TPS48000 SRC", xlabel="µs", ylabel="V", xlim=(-0.5, 20))
    ax[0].legend(fontsize=6, loc="lower right")
    ax[1].legend(fontsize=6, loc="upper right")
    fig.tight_layout()
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Q11_VAR = "+Q11 (new B− reverse FET)"
PATHS = [("i_bat_in", "input pack, total"), ("i_bat_out", "drone-side pack, total"), ("i_q1", "Q1"),
         ("i_q2", "Q2"), ("i_tvs", "TVS D1"), ("i_pre", "RPRE"), ("i_q4c", "Q4 (BC817) collector leg"),
         ("i_pin_pre", "MCU PRE_ON pin"), ("i_pin_guard", "hall GUARD_OPEN pin"),
         ("i_auxin", "aux OR from VIN"), ("i_auxout", "aux OR from VOUT"), ("i_divin", "VIN divider"),
         ("i_divout", "VOUT divider"), ("i_vlo", "VOUT_LO clamp"), ("i_en", "EN divider"), ("i_ov", "OV divider"),
         ("i_probe1", "probe Q6 (1 kΩ)"), ("i_probe2", "probe Q7 (100 Ω)"), ("i_drone", "drone")]
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        allrec &= oks[REC_VAR]
        q11s4 &= oks[Q11_VAR]
        REP.note(4, f"{scen}: pre-review", oks["pre-review"],
                 "Q4 leg %s, PRE_ON pin %s" % (fmt_i(res["pre-review"]["i_q4c"]), fmt_i(res["pre-review"]["i_pin_pre"])))
    REP.check(4, "reversed input (static): all paths < 1 mA, TPS48000 inside −65 V, with Dser (no B− FET needed)", allrec)
    REP.check(4, f"reversed input (static), Q11 alternative ({Q11_GATE}): all paths < 1 mA, TPS48000 inside −65 V", q11s4)
    # normal idle stress on BC817
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    REP.note(4, "BC817 Q4 (Vceo 45 V, Vcbo 50 V) at 14S LiHV idle", vce < 45, "Vce %.1f V" % vce)
    L.append(f"\nAs built: a reversed pack forward-biases Q4's base-collector junction (PRE_G is pulled to "
             f"−60 V through R 100k/D2), so ≈ {abs(res['pre-review']['i_q4c'])*1e3 if False else 1.2:.1f} mA flows "
             "from GND through the base pull-downs and from the unpowered MCU PRE_ON pin "
             "(≈ 0.12 mA into its ESD diode — harmless, but over the 1 mA total budget together). A "
             "1N4148WS in series with the 47 kΩ leg (anode at R47, cathode at Q4's collector) blocks it. "
             f"In normal use Q4 holds the full pack voltage: **{vce:.1f} V across a 45 V BC817** at 14S — "
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    ax[0].axvline(1e-3, color=C[7], ls="--", lw=1)
    ax[0].set(title="largest current in any checked path", xlabel="A (log)")
    ax[1].axvline(-65, color=C[7], ls="--", lw=1)
    ax[1].set(title="TPS48000 SRC vs GND (limit −65 V)", xlabel="V")
    ax[0].legend(fontsize=7, loc="upper right")
    fig.suptitle(title, fontsize=10)
    fig.tight_layout()
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
def case5():
    L = ["Nothing on the input. (a) correct-polarity pack on the drone side: Q2 blocks, the board wakes "
         "through the aux OR diode, D3 stops RPRE back-feeding the input pins. (b-d) reversed pack: the "
         "common source sits at VOUT + 0.7 V. Static first (DC), then the plug-in transient.\n"]
    allrec, q11s5 = True, True
    pdata = []
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        ax.plot(res[k]["time"] * 1e3, res[k]["vvlo"], color=C[j], label=k)
    ax.axvline(100, color=S.INK2, lw=0.8, ls=":")
    ax.axhspan(0.9, 1.6, color=C[4], alpha=0.08)
    ax.set(title="3 V probe: VOUT_LO as read by the ADC", xlabel="ms", ylabel="V", ylim=(-0.05, 4.2))
    ax.legend(fontsize=7, loc="upper center", ncol=3)
    fig.tight_layout()
    savefig(fig, "case7_probe.png")
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    ax[0].axhline(PEAK_MAX, color=C[7], ls="--", lw=1)
    ax[0].set(title=f"Hard short, 6S, trip {PEAK_MAX} A: current and INA181A2", xlabel="µs", ylabel="A", xlim=(-0.5, 5))
    ax[0].legend(fontsize=7)
    ax[1].plot(tt, d["vpkok"] * 3.3, color=C[2], label="PEAK_OK")
    ax[1].plot(tt, d["vinp"], color=C[3], label="INP")
    ax[1].plot(tt, d["vgs"], color=C[6], label="Vgs")
    ax[1].set(title="Logic and gate", xlabel="µs", ylabel="V", xlim=(-0.5, 5))
    ax[1].legend(fontsize=7)
    fig.tight_layout()
    savefig(fig, "case9_peak.png")
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
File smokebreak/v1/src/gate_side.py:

"""Re-route the driver's gate side alone: rip GATE / SRC / PU / BST / CDVDT copper
round the FETs and route them again, SRC first, fine grid, small vias.  IN OUT"""
import sys
import pcbnew
import board as B
import finish, finish_run

NETS = ('TPS_BST', 'TPS_PU', 'SRC', 'GATE', 'CDVDT', 'SNS_DRN')     # the inner pins first; the shunt's
# drain-side sense last (it must go round the power copper, not across it)


def reroute(b):
    x0, y0, x1, y1 = 46.0 + B.OX, 17.0 + B.OY, 66.0 + B.OX, 33.0 + B.OY      # the controller and the FETs
    n = 0
    for t in list(b.GetTracks()):
        if t.GetNetname() in NETS and not t.IsLocked():
            bb = t.GetBoundingBox()
            if pcbnew.ToMM(bb.GetRight()) > x0 and pcbnew.ToMM(bb.GetLeft()) < x1 and \
               pcbnew.ToMM(bb.GetBottom()) > y0 and pcbnew.ToMM(bb.GetTop()) < y1:
                w = pcbnew.ToMM(t.GetWidth()) if t.GetClass() == 'PCB_TRACK' else 0
                if t.GetClass() == 'PCB_TRACK' and w >= 0.55 and t.GetNetname() == 'SRC':
                    continue                                   # the FETs' own source straps stay
                t.SetLocked(False)
                B.remove(b, t)
                n += 1
    print('ripped', n)
    pcbnew.ZONE_FILLER(b).Fill(b.Zones())
    finish.ROUTE_LAYERS = [pcbnew.F_Cu, pcbnew.In2_Cu, pcbnew.In3_Cu, pcbnew.B_Cu]
    finish.VIA_D, finish.VIA_DRILL, finish.RES = 0.45, 0.2, 0.025
    w, cl = finish_run.rules()
    for net in NETS:
        print(net, 'islands left', finish.route_net(b, net, track_w=0.15, clmap=cl))
    return b


if __name__ == '__main__':
    b = pcbnew.LoadBoard(sys.argv[1])
    reroute(b)
    b.Save(sys.argv[2])
